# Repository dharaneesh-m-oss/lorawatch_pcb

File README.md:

# LoRa Wearable IoT PCB

A compact, low-power **LoRa-enabled wearable IoT hardware platform** designed using **KiCad**. This PCB was developed by transforming our **Smart India Hackathon (SIH)** prototype into a custom embedded hardware solution.

The board integrates long-range communication, motion sensing, environmental monitoring, GPS connectivity, battery charging, and onboard power management into a compact PCB suitable for wearable and portable IoT applications.

---

## Features

* ESP32-WROOM-32E Microcontroller
* LoRa RA-02 (SX1278) Long Range Communication
* GPS Interface
* MPU6050 6-Axis IMU
* BME280 Temperature, Humidity & Pressure Sensor
* USB Type-C Power Input
* TP4056 Li-ion Battery Charging
* 3.3V Voltage Regulation
* WS2812B Programmable RGB Status LED
* SOS Push Button
* Active Buzzer
* Compact PCB Layout
* Designed in KiCad

---

## Hardware Specifications

| Component            | Description               |
| -------------------- | ------------------------- |
| MCU                  | ESP32-WROOM-32E           |
| LoRa                 | Ai-Thinker RA-02 (SX1278) |
| Motion Sensor        | MPU6050                   |
| Environmental Sensor | BME280                    |
| Battery Charger      | TP4056                    |
| Voltage Regulator    | AMS1117-3.3               |
| Communication        | LoRa + UART + I²C + SPI   |
| Power Input          | USB Type-C                |
| Power Source         | 3.7V Li-ion Battery       |

---

## Project Structure

```text
LoRa-Wearable-PCB/
│
├── Hardware/
│   ├── Schematic
│   ├── PCB Layout
│   ├── 3D PCB Model
│   └── Libraries
│
├── Images/
│   ├── PCB_3D.png
│   ├── PCB_Top.png
│   ├── PCB_Bottom.png
│   └── Schematic.png
│
├── Manufacturing/
│   ├── Gerber Files
│   ├── Drill Files
│   ├── BOM
│   └── Pick and Place
│
└── README.md
```

---

## Interfaces

### SPI

* LoRa RA-02

### I²C

* MPU6050
* BME280

### UART

* GPS Module

### GPIO

* WS2812B RGB LED
* SOS Button
* Active Buzzer

---

## Software Support

* Arduino IDE
* PlatformIO
* ESP-IDF

---

## Applications

* Smart India Hackathon Projects
* Wearable IoT Devices
* Emergency Communication Systems
* Disaster Management
* Environmental Monitoring
* Asset Tracking
* Wildlife Monitoring
* Smart Agriculture
* Remote Data Acquisition

---

## Design Software

* KiCad

---

## Current Status

* ✅ Schematic Completed
* ✅ PCB Layout Completed
* ✅ 3D PCB Model Completed
* ⏳ PCB Fabrication
* ⏳ Assembly
* ⏳ Firmware Development
* ⏳ Hardware Validation

---

## Future Improvements

* Replace AMS1117 with a low-power LDO
* Add battery protection IC
* Integrate USB-UART programmer
* Optimize RF layout
* Reduce PCB size
* Improve power efficiency

---

## License

This project is released under the MIT License.

---

## Acknowledgement

This project originated as a **Smart India Hackathon (SIH)** prototype and has evolved into a custom PCB through continuous design improvements and embedded hardware development.

---

### If you found this project interesting, consider giving the repository a ⭐.

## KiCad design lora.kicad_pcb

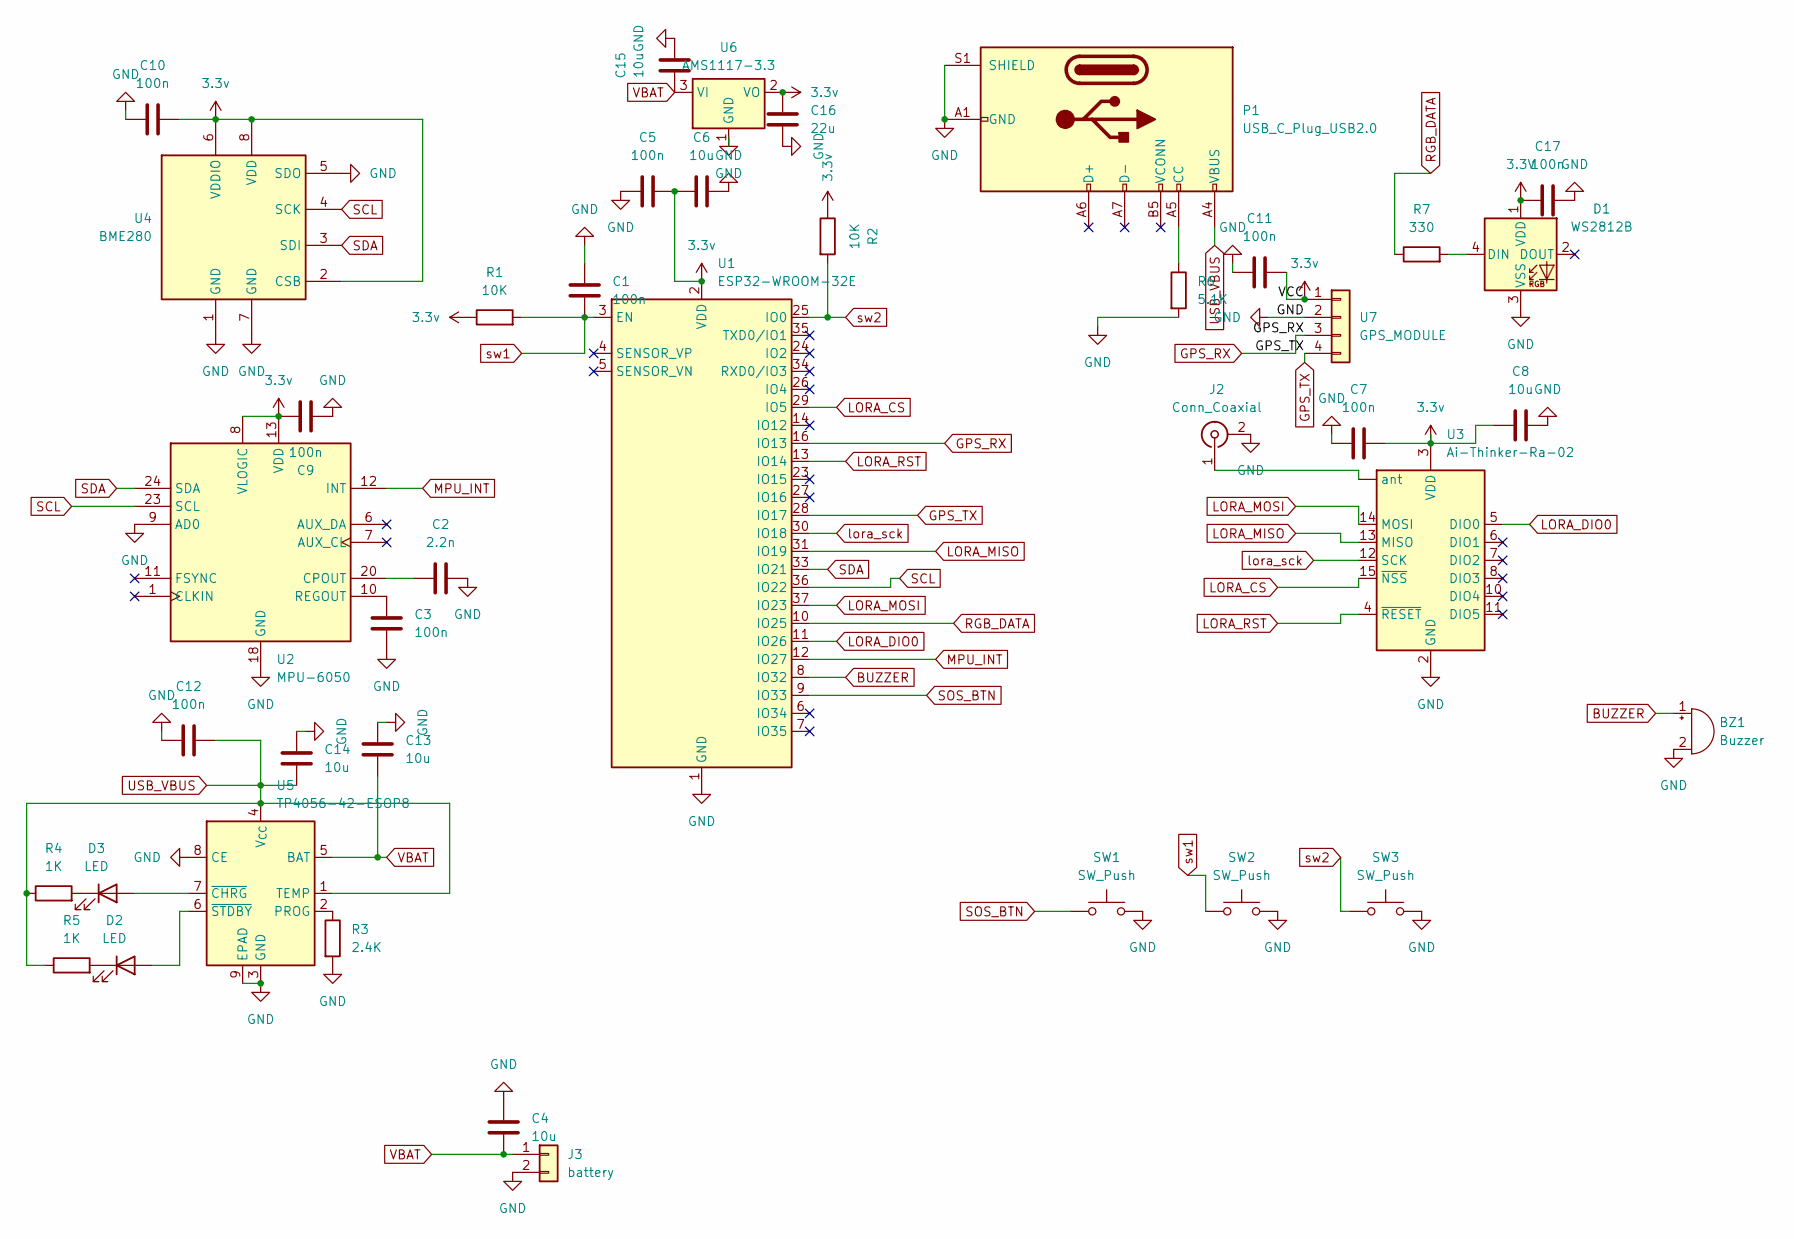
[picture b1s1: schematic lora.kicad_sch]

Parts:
BZ1: Buzzer; Buzzer_12x9.5RM7.6
C1, C3, C5, C7, C9, C10, C11, C12, C17: 100n; C_0603_1608Metric
C2: 2.2n; C_0603_1608Metric
C4, C6, C8, C13, C14, C15: 10u; C_0805_2012Metric
C16: 22u; C_1206_3216Metric
D1: WS2812B; LED_WS2812B_PLCC4_5.0x5.0mm_P3.2mm
D2, D3: LED; LED_0603_1608Metric
J2: Conn_Coaxial; U.FL_Hirose_U.FL-R-SMT-1_Vertical
J3: battery; JST_PH_B2B-PH-K_1x02_P2.00mm_Vertical
P1: USB_C_Plug_USB2.0; USB_C_Receptacle_HRO_TYPE-C-31-M-12
R1, R2: 10K; R_0603_1608Metric
R3: 2.4K; R_0603_1608Metric
R4, R5: 1K; R_0603_1608Metric
R6: 5.1K; R_0603_1608Metric
R7: 330; R_0603_1608Metric
SW1, SW2, SW3: SW_Push; SW_SPST_TL3342
U1: ESP32-WROOM-32E; ESP32-WROOM-32D
U2: MPU-6050; InvenSense_QFN-24_4x4mm_P0.5mm
U3: Ai-Thinker-Ra-02; Ai-Thinker-Ra-01-LoRa
U4: BME280; Bosch_LGA-8_2.5x2.5mm_P0.65mm_ClockwisePinNumbering
U5: TP4056-42-ESOP8; SOIC-8-1EP_3.9x4.9mm_P1.27mm_EP2.41x3.3mm_ThermalVias
U6: AMS1117-3.3; SOT-223-3_TabPin2
U7: GPS_MODULE; JST_PH_B4B-PH-K_1x04_P2.00mm_Vertical

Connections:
3.3V: C17.2, D1.1 (VDD)
3.3v: C5.2, C6.2, C7.2, C8.2, C9.2, C10.2, C11.2, C16.2, R1.1, R2.1, U1.2 (VDD), U2.8 (VLOGIC), U2.13 (VDD), U3.3 (VDD), U4.2 (CSB), U4.6 (VDDIO), U4.8 (VDD), U6.2 (VO), U7.1
BUZZER: BZ1.1 (+), U1.8 (IO32)
GND: BZ1.2 (-), C1.1, C2.2, C3.2, C4.1, C5.1, C6.1, C7.1, C8.1, C9.1, C10.1, C11.1, C12.1, C13.1, C14.1, C15.1, C16.1, C17.1, D1.3 (VSS), J2.2 (Ext), J3.2, P1.A1 (GND), P1.A12 (GND), P1.B1 (GND), P1.B12 (GND), P1.S1 (SHIELD), R3.2, R6.2, SW1.2, SW2.2, SW3.2, U1.1 (GND), U1.15 (GND), U1.38 (GND), U1.39 (GND), U2.9 (AD0), U2.18 (GND), U3.1 (GND), U3.2 (GND), U3.9 (GND), U3.16 (GND), U4.1 (GND), U4.5 (SDO), U4.7 (GND), U5.3 (GND), U5.8 (CE), U5.9 (EPAD), U6.1 (GND), U7.2
GPS_RX: U1.16 (IO13), U7.3
GPS_TX: U1.28 (IO17), U7.4
LORA_CS: U1.29 (IO5), U3.15 (~NSS)
LORA_DIO0: U1.11 (IO26), U3.5 (DIO0)
LORA_MISO: U1.31 (IO19), U3.13 (MISO)
LORA_MOSI: U1.37 (IO23), U3.14 (MOSI)
LORA_RST: U1.13 (IO14), U3.4 (~RESET)
MPU_INT: U1.12 (IO27), U2.12 (INT)
unnamed: D1.4 (DIN), R7.2
unnamed: D2.2 (A), U5.6 (~STDBY)
unnamed: D2.1 (K), R5.2
unnamed: D3.2 (A), U5.7 (~CHRG)
unnamed: D3.1 (K), R4.2
unnamed: J2.1 (In), U3. (ant)
unnamed: P1.A5 (CC), R6.1
unnamed: C2.1, U2.20 (CPOUT)
unnamed: C3.1, U2.10 (REGOUT)
unnamed: R3.1, U5.2 (PROG)
RGB_DATA: R7.1, U1.10 (IO25)
SCL: U1.36 (IO22), U2.23 (SCL), U4.4 (SCK)
SDA: U1.33 (IO21), U2.24 (SDA), U4.3 (SDI)
SOS_BTN: SW1.1, U1.9 (IO33)
USB_VBUS: C12.2, C14.2, P1.A4 (VBUS), P1.A9 (VBUS), P1.B4 (VBUS), P1.B9 (VBUS), R4.1, R5.1, U5.1 (TEMP), U5.4 (V_{CC})
VBAT: C4.2, C13.2, C15.2, J3.1, U5.5 (BAT), U6.3 (VI)
lora_sck: U1.30 (IO18), U3.12 (SCK)
sw1: C1.2, R1.2, SW2.1, U1.3 (EN)
sw2: R2.2, SW3.1, U1.25 (IO0)

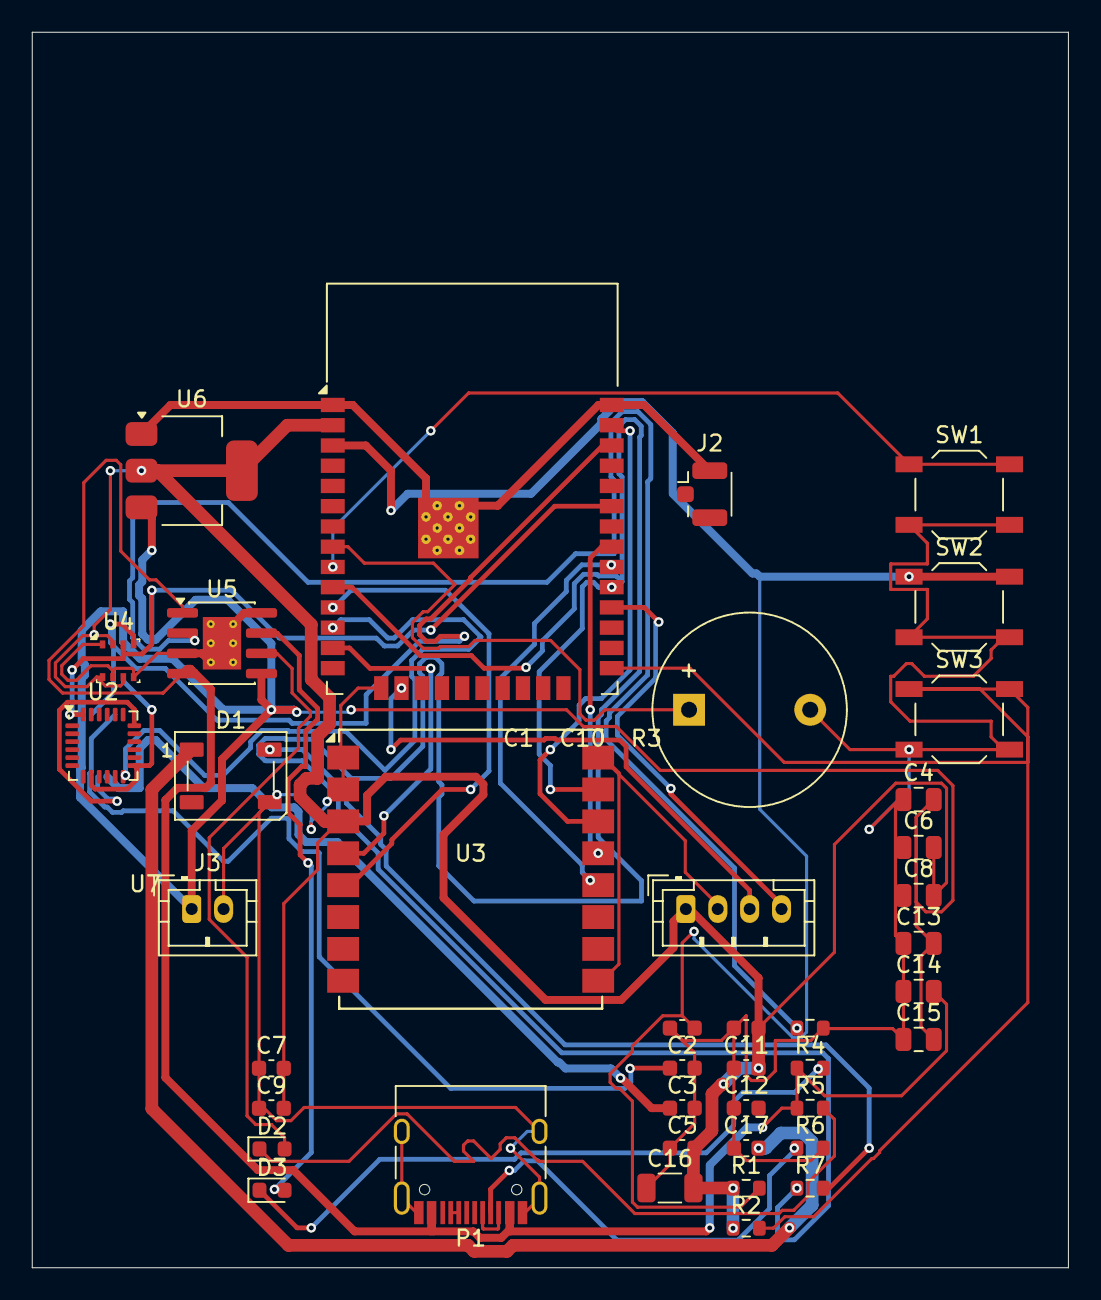
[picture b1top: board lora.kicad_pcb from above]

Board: 2 copper layers, 65.0 x 77.5 mm, 41 parts (0 on the bottom side), 30 nets.

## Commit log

2026-06-25 Add README for LoRa Wearable IoT PCB project
    Add detailed project information for LoRa Wearable IoT PCB including features, specifications, project structure, interfaces, software support, applications, current status, future improvements, and 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
